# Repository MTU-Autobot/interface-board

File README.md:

# interface-board

Interface board for MTU's IGVC robot. The board connects to an RC controller, wheel encoders, motor controllers, and status lights and is controlled over USB. The microcontroller is a MK20DX256 running a Teensy 3.2 bootloader for easy programming. Main power conversion is handled by a TPS62143 buck converter and can handle up to 17 volts in for compatibility with 12 volt systems.

To interface with the board you need to setup the udev rules found [here](https://www.pjrc.com/teensy/loader_linux.html)

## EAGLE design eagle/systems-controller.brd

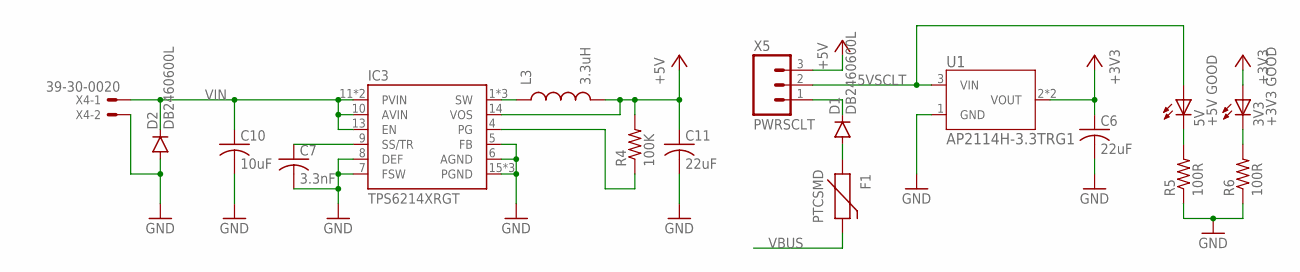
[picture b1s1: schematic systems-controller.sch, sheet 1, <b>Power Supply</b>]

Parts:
3V3: +3V3 GOOD; SML0603
5V: +5V GOOD; SML0603
C6, C11: 22uF; C0805K
C7: 3.3nF; C0603K
C10: 10uF; C0805K
D1, D2: DB2460600L; SOD-128
F1: PTCSMD; PTC-1206
IC3: TPS6214XRGT; 16-VQFN
L3: 3.3uH; SRN5020
R4: 100K; R0603
R5, R6: 100R; R0603
U1: AP2114H-3.3TRG1; SOT-223
X4: 39-30-0020
X5: PWRSCLT; 1X03

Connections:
5VSCLT: 5V.A, U1.3 (VIN), X5.2
+3V3: 3V3.A, C6.1, U1.2 (VOUT), U1.4 (VOUT); also elsewhere on the board
+5V: C11.1, IC3.14 (VOS), L3.2, R4.2, X5.3; also elsewhere on the board
GND: C6.2, C7.2, C10.2, C11.2, D2.A, IC3.5 (FB), IC3.6 (AGND), IC3.7 (FSW), IC3.8 (DEF), IC3.15 (PGND), IC3.16 (PGND), IC3.PAD (PGND), R5.1, R6.1, U1.1 (GND), X4.2; also elsewhere on the board
unnamed: IC3.4 (PG), R4.1
unnamed: C7.1, IC3.9 (SS/TR)
unnamed: D1.C, X5.1
unnamed: IC3.1 (SW), IC3.2 (SW), IC3.3 (SW), L3.1
unnamed: D1.A, F1.1
unnamed: 5V.C, R5.2
unnamed: 3V3.C, R6.2
VBUS: F1.2; also elsewhere on the board
VIN: C10.1, D2.C, IC3.10 (AVIN), IC3.11 (PVIN), IC3.12 (PVIN), IC3.13 (EN), X4.1; also elsewhere on the board

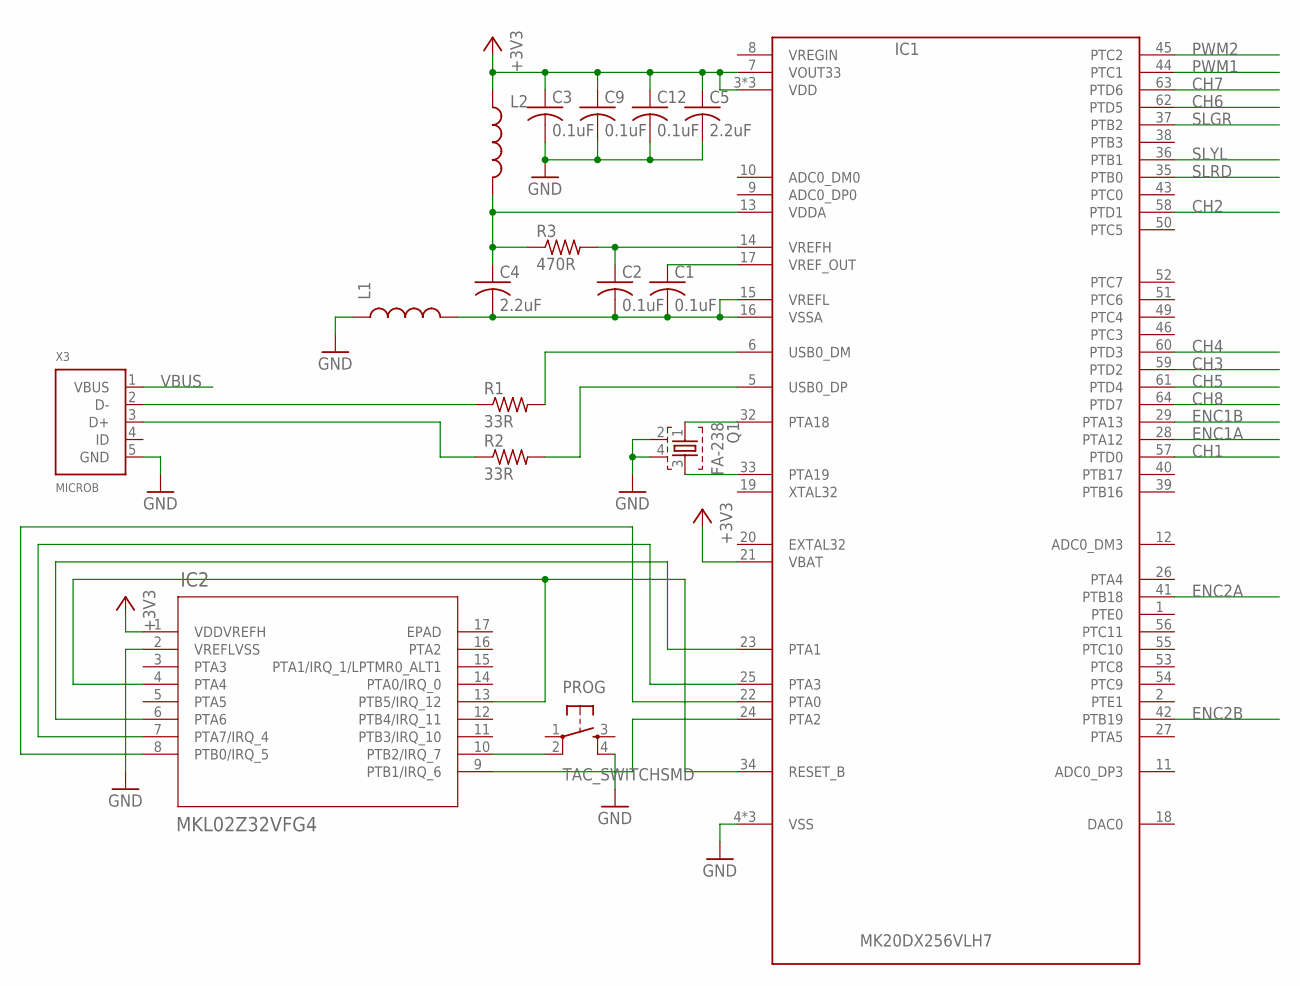
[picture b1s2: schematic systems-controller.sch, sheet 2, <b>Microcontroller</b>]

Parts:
C1, C2, C3, C9, C12: 0.1uF; C0603K
C4, C5: 2.2uF; C0603K
IC1: MK20DX256VLH7
IC2: MKL02Z32VFG4; QFN-16_3X3X0.65
L1, L2: INDUCTOR30OHM,1.8A; 0603
PROG: TAC_SWITCHSMD; TACTILE-SWITCH-SMD
Q1: FA-238
R1, R2: 33R; R0603
R3: 470R; R0603
X3: MICROB; 10118192

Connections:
+3V3: C3.1, C5.1, C9.1, C12.1, IC1.3 (VDD), IC1.7 (VOUT33), IC1.21 (VBAT), IC1.30 (VDD), IC1.48 (VDD), IC2.1 (VDDVREFH), L2.1; also elsewhere on the board
CH1: IC1.57 (PTD0); also elsewhere on the board
CH2: IC1.58 (PTD1); also elsewhere on the board
CH3: IC1.59 (PTD2); also elsewhere on the board
CH4: IC1.60 (PTD3); also elsewhere on the board
CH5: IC1.61 (PTD4); also elsewhere on the board
CH6: IC1.62 (PTD5); also elsewhere on the board
CH7: IC1.63 (PTD6); also elsewhere on the board
CH8: IC1.64 (PTD7); also elsewhere on the board
ENC1A: IC1.28 (PTA12); also elsewhere on the board
ENC1B: IC1.29 (PTA13); also elsewhere on the board
ENC2A: IC1.41 (PTB18); also elsewhere on the board
ENC2B: IC1.42 (PTB19); also elsewhere on the board
GND: C3.2, C5.2, C9.2, C12.2, IC1.4 (VSS), IC1.31 (VSS), IC1.47 (VSS), IC2.2 (VREFLVSS), L1.1, PROG.4, Q1.2, Q1.4, X3.5 (GND); also elsewhere on the board
unnamed: IC1.25 (PTA3), IC2.7 (PTA7/IRQ_4)
unnamed: IC1.22 (PTA0), IC2.8 (PTB0/IRQ_5)
unnamed: IC1.24 (PTA2), IC2.9 (PTB1/IRQ_6)
unnamed: IC1.23 (PTA1), IC2.6 (PTA6)
unnamed: IC1.34 (RESET_B), IC2.4 (PTA4), IC2.13 (PTB5/IRQ_12)
unnamed: R1.1, X3.2 (D-)
unnamed: IC1.6 (USB0_DM), R1.2
unnamed: R2.1, X3.3 (D+)
unnamed: IC1.5 (USB0_DP), R2.2
unnamed: IC1.32 (PTA18), Q1.1
unnamed: IC1.33 (PTA19), Q1.3
unnamed: C1.2, C2.2, C4.2, IC1.15 (VREFL), IC1.16 (VSSA), L1.2
unnamed: C1.1, IC1.17 (VREF_OUT)
unnamed: C2.1, IC1.14 (VREFH), R3.2
unnamed: C4.1, IC1.13 (VDDA), L2.2, R3.1
unnamed: IC2.10 (PTB2/IRQ_7), PROG.2
PWM1: IC1.44 (PTC1); also elsewhere on the board
PWM2: IC1.45 (PTC2); also elsewhere on the board
SLGR: IC1.37 (PTB2); also elsewhere on the board
SLRD: IC1.35 (PTB0); also elsewhere on the board
SLYL: IC1.36 (PTB1); also elsewhere on the board
VBUS: X3.1 (VBUS); also elsewhere on the board

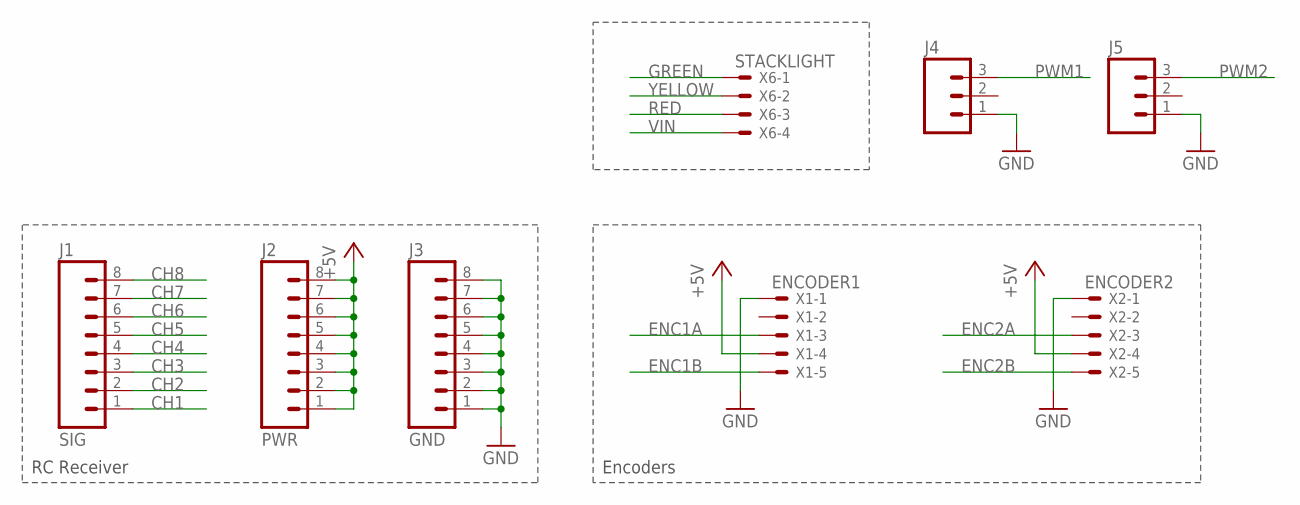
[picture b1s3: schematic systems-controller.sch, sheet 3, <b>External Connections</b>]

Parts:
J1: SIG; 1X08_ROUND
J2: PWR; 1X08_ROUND
J3: GND; 1X08_ROUND
J4, J5: M03PTH; 1X03
X1: ENCODER1; 70553-05
X2: ENCODER2; 70553-05
X6: STACKLIGHT; 70553-04

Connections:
+5V: J2.1, J2.2, J2.3, J2.4, J2.5, J2.6, J2.7, J2.8, X1.4, X2.4; also elsewhere on the board
CH1: J1.1; also elsewhere on the board
CH2: J1.2; also elsewhere on the board
CH3: J1.3; also elsewhere on the board
CH4: J1.4; also elsewhere on the board
CH5: J1.5; also elsewhere on the board
CH6: J1.6; also elsewhere on the board
CH7: J1.7; also elsewhere on the board
CH8: J1.8; also elsewhere on the board
ENC1A: X1.3; also elsewhere on the board
ENC1B: X1.5; also elsewhere on the board
ENC2A: X2.3; also elsewhere on the board
ENC2B: X2.5; also elsewhere on the board
GND: J3.1, J3.2, J3.3, J3.4, J3.5, J3.6, J3.7, J3.8, J4.1, J5.1, X1.1, X2.1; also elsewhere on the board
GREEN: X6.1; also elsewhere on the board
PWM1: J4.3; also elsewhere on the board
PWM2: J5.3; also elsewhere on the board
RED: X6.3; also elsewhere on the board
VIN: X6.4; also elsewhere on the board
YELLOW: X6.2; also elsewhere on the board

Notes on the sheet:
RC Receiver
Encoders

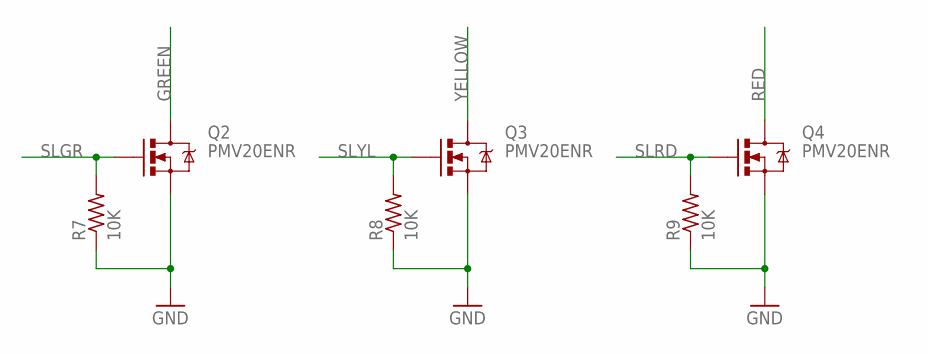
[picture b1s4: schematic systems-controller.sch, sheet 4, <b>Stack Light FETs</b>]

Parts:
Q2, Q3, Q4: PMV20ENR; SOT23-3
R7, R8, R9: 10K; R0603

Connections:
GND: Q2.2 (S), Q3.2 (S), Q4.2 (S), R7.1, R8.1, R9.1; also elsewhere on the board
GREEN: Q2.3 (D); also elsewhere on the board
RED: Q4.3 (D); also elsewhere on the board
SLGR: Q2.1 (G), R7.2; also elsewhere on the board
SLRD: Q4.1 (G), R9.2; also elsewhere on the board
SLYL: Q3.1 (G), R8.2; also elsewhere on the board
YELLOW: Q3.3 (D); also elsewhere on the board

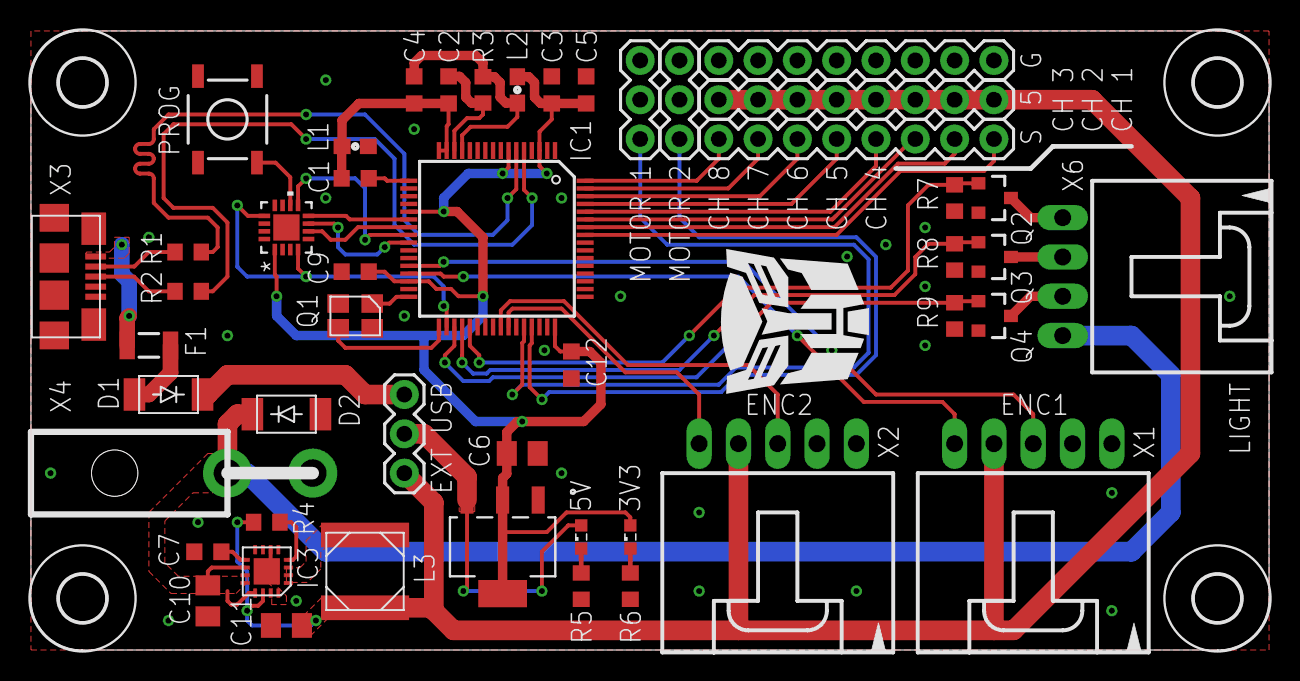
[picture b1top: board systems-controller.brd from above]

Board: 2 copper layers, 80.0 x 40.0 mm, 52 parts (0 on the bottom side), 49 nets.

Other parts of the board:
U$1, U$2, U$3, U$4: 3,0

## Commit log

2016-10-11 moved files hopefully
2016-10-12 added pwm headers
2016-10-12 made silkscreen pretty!
2016-10-12 tweaked silkscreen
2016-10-12 fixed silkscreen and un-tented via
2016-10-16 changed to usb serial
2016-10-16 moved rc stuff to new file
2016-10-16 renamed uart to serial
2016-10-17 pwm setup done maybe
2016-10-17 added set period function
2016-10-18 updating registers is dumb so you need to clear the SC one first
2016-10-18 added more to isr
2016-10-19 got encoders working with library, removed extra files
2016-10-21 isr to calculate speed at ever y1ms
2016-10-22 calculating motor values for manual control, cleaned up some misc things
2016-10-23 mode selection, estop stuff almost working
2016-10-23 fixed failsafe behavior
2016-10-23 some pid stuff, not sure how to implement yet
2016-10-23 move travis.yml
2016-10-23 update travis.yml, maybe last time?
2016-10-23 update travis.yml, please work
2016-10-23 Added build badge
2016-10-25 fixed reversed usb connector footprint
2016-10-25 update image
2016-10-25 how does git even work
2016-10-25 autobot logo :)
2016-10-27 moved failsafe to top to probably fix erratic behavior
2016-10-27 fixed reversed encoder connectors
2016-10-27 speed limit, blinking light, pull-downs
2016-10-29 fixed pwm
2016-10-29 lets try this
2016-11-02 rewrote serial read to not block
2016-11-03 added flush to serial print
2016-11-05 distance calculation started
2016-11-16 sending encoder data
2016-11-16 moved encoder update
2017-02-16 drive commands working, need to change scaling. code rewrite possible
2017-02-18 include pid library
2017-02-19 pid almost there, need to figure out mapping
2017-02-19 pid working i think, needs tuning now
2017-02-19 deleted old folder name
2017-03-02 Added part about udev rules
2017-03-15 added preprocessor pid switches
2017-03-15 add board image

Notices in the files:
parts and their libraries:
SparkFun-DiscreteSemi: Licensing: Creative Commons ShareAlike 4.0 International - https://creativecommons.org/licenses/by-sa/4.0
